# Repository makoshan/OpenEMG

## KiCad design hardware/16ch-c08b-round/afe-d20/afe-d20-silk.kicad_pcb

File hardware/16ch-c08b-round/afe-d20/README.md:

# C08B 16 通道双面采集板 `D20`（圆孔版，配螺丝壳 `R12`）

- **板框与工艺**：`43.10 × 36.50 mm`（四角 `R4.6 mm` 圆角 + 4 个 `Ø1.7 mm` 安装孔 `H901..H904`），4 层 `0.8 mm`（`JLC04081H-3313`），沉金，过孔盖油。
- **器件与接口**：正反双面双 `ADS1298` 同步采样（24 种物料共 127 颗贴片件，16 颗输入差分电容为 `22 pF` `C76924`），东南角 20P `0.5 mm` `J_AFE` 与主控板 `R4U6` 正对互联，双 34P 软板座连接 [`../strap-fpc-d2/`](../strap-fpc-d2/) 或 [`../strap-fpc-r15/`](../strap-fpc-r15/)。
- **打样与贴片投产三件套**：
  1. 工艺边拼板 Gerber：`panel/c08b-afe-d20-panel-gerber.zip`（`70.2 × 70.2 mm` 一拼一邮票孔工艺边，只传此拼板包，不传单板 `gerber/` 目录）
  2. 物料清单：`jlc_smt_bom.csv`
  3. 贴片坐标：`jlc_smt_cpl.csv`（采用单板原点，与拼板 Gerber 同坐标系；SMT 预览请核对 `V4_U2`、`V4_FPC3` 及 36 颗 ESD 极性方向）
- **三维模型与自检**：
  - 满载整板 STEP：`c08b-afe-d20-3d.step`（连接器模型随附于 `assembly/models/FPC2-fh34.step`）
  - 源板 `afe-d20-silk.kicad_pcb`（SHA-256 `31323826…`）：KiCad 10 DRC 0 违规 / 0 未连，`route_lint.py` 硬项全 0，`panel/check_panel.py` 通过。

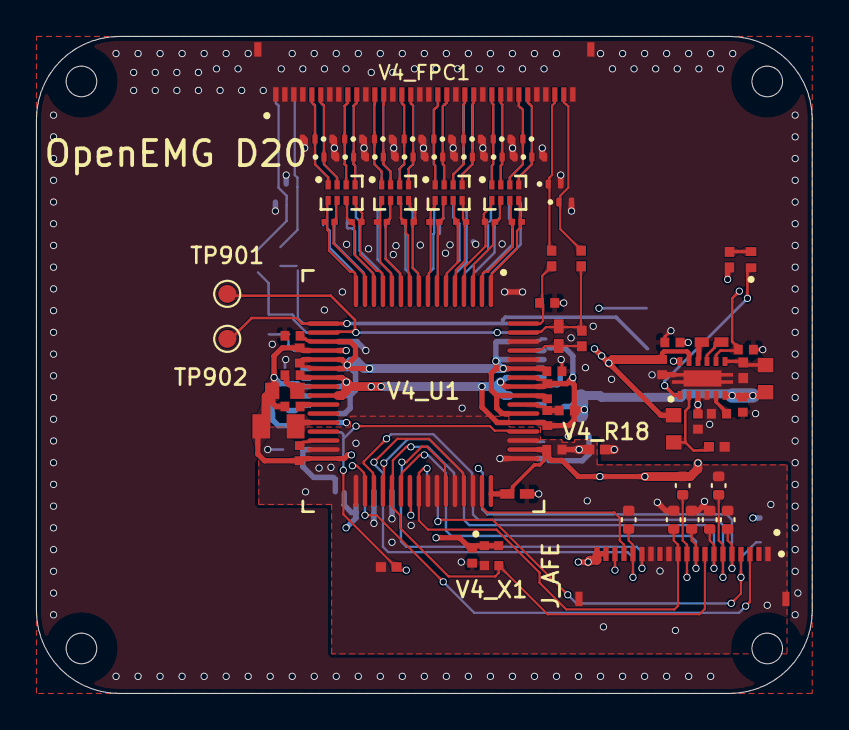
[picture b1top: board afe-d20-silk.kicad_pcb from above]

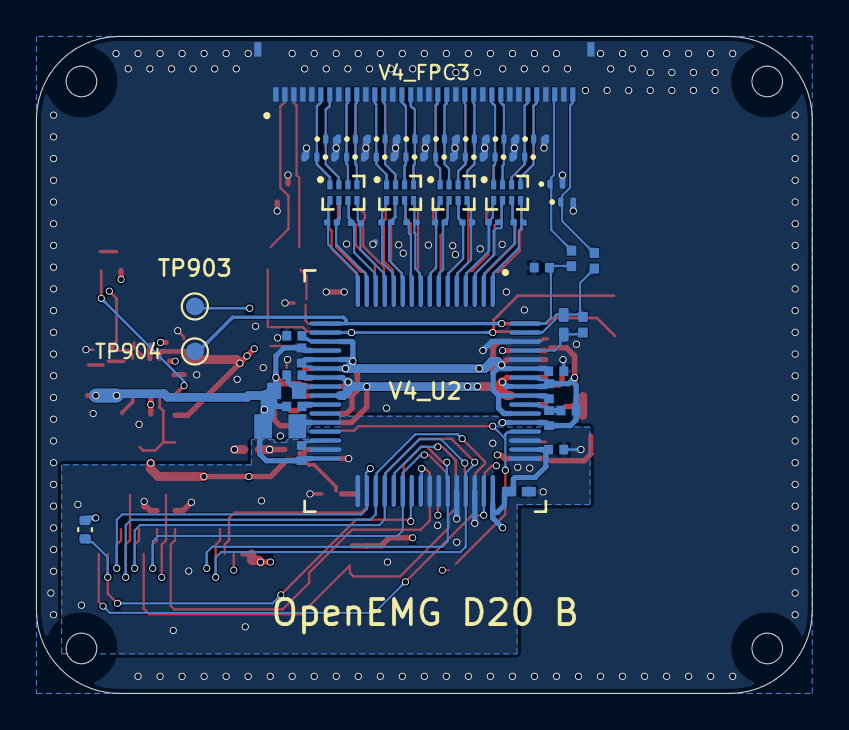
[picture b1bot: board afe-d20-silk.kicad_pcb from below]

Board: 4 copper layers, 43.1 x 36.5 mm, 135 parts (53 on the bottom side), 111 nets.

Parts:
C901: 10uF; C901
C902: 4.7uF; C902
D901: XL-1005UGC; D901
D910: ESD401DPYR; D910
D911: ESD401DPYR; D911
D912: ESD401DPYR; D912
D913: ESD401DPYR; D913
D914: ESD401DPYR; D914
D915: ESD401DPYR; D915
D916: ESD401DPYR; D916
D917: ESD401DPYR; D917
D918: ESD401DPYR; D918
D919: ESD401DPYR; D919
D920: ESD401DPYR; D920
D921: ESD401DPYR; D921
D922: ESD401DPYR; D922
D923: ESD401DPYR; D923
D924: ESD401DPYR; D924
D925: ESD401DPYR; D925
D926: ESD401DPYR; D926
D927: ESD401DPYR; D927
D930: ESD401DPYR; D930
D931: ESD401DPYR; D931
D932: ESD401DPYR; D932
D933: ESD401DPYR; D933
D934: ESD401DPYR; D934
D935: ESD401DPYR; D935
D936: ESD401DPYR; D936
D937: ESD401DPYR; D937
D938: ESD401DPYR; D938
D939: ESD401DPYR; D939
D940: ESD401DPYR; D940
D941: ESD401DPYR; D941
D942: ESD401DPYR; D942
D943: ESD401DPYR; D943
D944: ESD401DPYR; D944
D945: ESD401DPYR; D945
D946: ESD401DPYR; D946
D947: ESD401DPYR; D947
H901: M1.4 NPTH 1.7; H901
H902: M1.4 NPTH 1.7; H902
H903: M1.4 NPTH 1.7; H903
H904: M1.4 NPTH 1.7; H904
J_AFE: FH34SRJ-20S-0.5SH(50) (LCSC C2802370); Hirose_FH34SRJ-20S-0.5SH
R801: 10k; R801
R802: 10k; R802
R803: 10k; R803
R804: 10k; R804
R805: 10k; R805
R806: 10k; R806
R807: 10k; R807
R808: 10k; R808
R901: 10kΩ; R901
TP901: V4_REF2; TP901
TP902: V4_REF1; TP902
TP903: V4_REF2; TP903
TP904: V4_REF1; TP904
V4_C31: 1uF; V4_C31
V4_C32: 100nF; V4_C32
V4_C33: 1uF; V4_C33
V4_C34: 100nF; V4_C34
V4_C35: 1uF; V4_C35
V4_C36: 100nF; V4_C36
V4_C37: 100nF; V4_C37
V4_C43: 1uF; V4_C43
V4_C44: 1uF; V4_C44
V4_C45: 100nF; V4_C45
V4_C46: 10uF; V4_C46
V4_C47: 10nF; V4_C47
V4_C48: 100nF; V4_C48
V4_C49: 1uF; V4_C49
V4_C50: 100nF; V4_C50
V4_C54: 22uF; V4_C54
V4_C72: 22pF; V4_C72
V4_C73: 22pF; V4_C73
V4_C74: 22pF; V4_C74
V4_C75: 22pF; V4_C75
V4_C76: 22pF; V4_C76
V4_C77: 22pF; V4_C77
V4_C78: 22pF; V4_C78
V4_C79: 22pF; V4_C79
V4_C81: 100nF; V4_C81
V4_C82: 100nF; V4_C82
V4_C83: 2.2uF; V4_C83
V4_C84: 2.2uF; V4_C84
V4_C85: 1uF; V4_C85
V4_C86: 1uF; V4_C86
V4_C87: 100nF; V4_C87
V4_C88: 10uF; V4_C88
V4_C89: 10nF; V4_C89
V4_C90: 100nF; V4_C90
V4_C91: 1uF; V4_C91
V4_C92: 22uF; V4_C92
V4_C109: 22pF; V4_C109
V4_C110: 22pF; V4_C110
V4_C111: 22pF; V4_C111
V4_C112: 22pF; V4_C112
V4_C113: 22pF; V4_C113
V4_C114: 22pF; V4_C114
V4_C115: 22pF; V4_C115
V4_C116: 22pF; V4_C116
V4_C117: 1uF; V4_C117
V4_C118: 100nF; V4_C118
V4_C119: 1uF; V4_C119
V4_C120: 100nF; V4_C120
V4_C121: 1uF; V4_C121
V4_C122: 100nF; V4_C122
V4_C123: 100pF; V4_C123
V4_C124: 100pF; V4_C124
V4_FPC1, V4_FPC3: FH34SRJ-34S-0.5SH(50) (LCSC C424660); Hirose_FH34SRJ-34S-0.5SH
V4_LM27762: LM27762DSSR; V4_LM27762
V4_R17: 10K; V4_R17
V4_R18: 0R; V4_R18
V4_R24: 392K; V4_R24
V4_R26: 107k; V4_R26
V4_R27: 100kΩ; V4_R27
V4_R28: 100kΩ; V4_R28
V4_R29: 104k; V4_R29
V4_R32: 392K; V4_R32
V4_R34: 392K; V4_R34
V4_R35: 10K; V4_R35
V4_R36: 392K; V4_R36
V4_R37: 10K; V4_R37
V4_U1: ADS1298IPAGR; V4_U1
V4_U2: ADS1298IPAGR; V4_U2
V4_U3: 15kΩ; V4_U3
V4_U4: 15kΩ; V4_U4
V4_U5: 15kΩ; V4_U5
V4_U6: 15kΩ; V4_U6
V4_U7: 15kΩ; V4_U7
V4_U8: 15kΩ; V4_U8
V4_U9: 15kΩ; V4_U9
V4_U10: 15kΩ; V4_U10
V4_X1: 2.048MHz; V4_X1

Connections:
3V3: C901.2, J_AFE.19, J_AFE.20, R801.2, R802.2, R901.1, V4_C31.2, V4_C32.2, V4_C37.2, V4_C81.2, V4_C82.2, V4_C117.2, V4_C118.2, V4_LM27762.3, V4_LM27762.8, V4_LM27762.12, V4_U1.48, V4_U1.50, V4_U2.48, V4_U2.50, V4_X1.1, V4_X1.4
ADS_CLKSEL: J_AFE.18, V4_R17.2, V4_U1.52, V4_U2.52
ADS_CS_A: J_AFE.10, R801.1, V4_U1.39
ADS_CS_B: J_AFE.4, R802.1, V4_U2.39
ADS_DRDY_A: J_AFE.17, V4_U1.47
ADS_DRDY_B: J_AFE.3, V4_U2.47
ADS_PWDN: J_AFE.6, R804.1, V4_U1.35, V4_U2.35
ADS_RESET: J_AFE.7, R803.1, V4_U1.36, V4_U2.36
ADS_START: J_AFE.9, R805.1, V4_U1.38, V4_U2.38
AFE_CLK_IN: J_AFE.8, V4_U1.37, V4_U2.37, V4_X1.3
AFE_GPIO3: J_AFE.16, R808.1, V4_U1.45, V4_U2.45
AGND: C901.1, C902.1, D910.2, D911.2, D912.2, D913.2, D914.2, D915.2, D916.2, D917.2, D918.2, D919.2, D920.2, D921.2, D922.2, D923.2, D924.2, D925.2, D926.2, D927.2, D930.2, D931.2, D932.2, D933.2, D934.2, D935.2, D936.2, D937.2, D938.2, D939.2, D940.2, D941.2, D942.2, D943.2, D944.2, D945.2, D946.2, D947.2, V4_C33.1, V4_C34.1, V4_C81.1, V4_C82.1, V4_C83.1, V4_C84.1, V4_C119.1, V4_C120.1, V4_C123.2, V4_C124.2, V4_FPC1.1, V4_FPC1.2, V4_FPC1.3, V4_FPC1.4, V4_FPC1.7, V4_FPC1.8, V4_FPC1.11, V4_FPC1.14, V4_FPC1.17, V4_FPC1.18, V4_FPC1.21, V4_FPC1.24, V4_FPC1.27, V4_FPC1.30, V4_FPC1.31, V4_FPC1.34, V4_FPC1.MP, V4_FPC3.1, V4_FPC3.2, V4_FPC3.3, V4_FPC3.4, V4_FPC3.5, V4_FPC3.8, V4_FPC3.11, V4_FPC3.14, V4_FPC3.17, V4_FPC3.18, V4_FPC3.21, V4_FPC3.24, V4_FPC3.27, V4_FPC3.28, V4_FPC3.31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
DIN_B: J_AFE.5, R807.1, V4_U1.34, V4_U2.34
DOUT_B: J_AFE.15, V4_U1.43, V4_U2.43
GND: J_AFE.1, J_AFE.12, J_AFE.14, J_AFE.21, J_AFE.22, R803.2, R804.2, R805.2, R806.2, R807.2, R808.2, V4_C31.1, V4_C32.1, V4_C37.1, V4_C117.1, V4_C118.1, V4_R17.1, V4_R18.1, V4_U1.31, V4_U1.33, V4_U1.41, V4_U1.42, V4_U1.44, V4_U1.46, V4_U1.49, V4_U1.51, V4_U2.31, V4_U2.33, V4_U2.41, V4_U2.42, V4_U2.44, V4_U2.46, V4_U2.49, V4_U2.51, V4_X1.2
SCLK_B: J_AFE.11, R806.1, V4_U1.40, V4_U2.40
V4_$1N19: V4_C45.2, V4_C46.1, V4_U1.24
V4_$1N24: V4_C44.2, V4_U1.26
V4_$1N25: V4_C54.2, V4_U1.28
V4_$1N26: V4_C43.2, V4_U1.30
V4_$1N44: V4_C48.2, V4_C49.1, V4_U1.55
V4_$1N307: V4_C85.2, V4_U2.30
V4_$1N308: V4_C92.2, V4_U2.28
V4_$1N309: V4_C86.2, V4_U2.26
V4_$1N319: V4_C87.2, V4_C88.1, V4_U2.24
V4_$1N323: V4_C90.2, V4_C91.1, V4_U2.55
V4_$1N350: V4_C123.1, V4_R35.1, V4_U1.64
V4_$1N353: V4_C124.1, V4_R37.1, V4_U2.64
V4_$2N83: D927.1, V4_FPC1.5, V4_U6.1
V4_$2N85: D926.1, V4_FPC1.6, V4_U6.2
V4_$2N86: D925.1, V4_FPC1.9, V4_U6.3
V4_$2N87: D924.1, V4_FPC1.10, V4_U6.4
V4_$2N90: D921.1, V4_FPC1.15, V4_U5.3
V4_$2N93: D918.1, V4_FPC1.20, V4_U4.2
V4_$2N94: D917.1, V4_FPC1.22, V4_U4.3
V4_$2N95: D916.1, V4_FPC1.23, V4_U4.4
V4_$2N96: D915.1, V4_FPC1.25, V4_U3.1
V4_$2N97: D914.1, V4_FPC1.26, V4_U3.2
V4_$2N98: D913.1, V4_FPC1.28, V4_U3.3
V4_$2N111: D919.1, V4_FPC1.19, V4_U4.1
V4_$2N118: D923.1, V4_FPC1.12, V4_U5.1
V4_$2N119: D922.1, V4_FPC1.13, V4_U5.2
V4_$2N120: D920.1, V4_FPC1.16, V4_U5.4
V4_$2N121: D912.1, V4_FPC1.29, V4_U3.4
V4_$2N324: D932.1, V4_FPC3.30, V4_U7.4
V4_$2N325: D940.1, V4_FPC3.16, V4_U9.4
V4_$2N326: D942.1, V4_FPC3.13, V4_U9.2
V4_$2N327: D943.1, V4_FPC3.12, V4_U9.1
V4_$2N330: D939.1, V4_FPC3.19, V4_U8.1
V4_$2N331: D933.1, V4_FPC3.29, V4_U7.3
V4_$2N332: D934.1, V4_FPC3.26, V4_U7.2
V4_$2N333: D935.1, V4_FPC3.25, V4_U7.1
V4_$2N334: D936.1, V4_FPC3.23, V4_U8.4
V4_$2N335: D937.1, V4_FPC3.22, V4_U8.3
V4_$2N336: D938.1, V4_FPC3.20, V4_U8.2
V4_$2N337: D941.1, V4_FPC3.15, V4_U9.3
V4_$2N338: D944.1, V4_FPC3.10, V4_U10.4
V4_$2N339: D945.1, V4_FPC3.9, V4_U10.3
V4_$2N340: D946.1, V4_FPC3.7, V4_U10.2
V4_$2N341: D947.1, V4_FPC3.6, V4_U10.1
V4_$3N49: D901.2, R901.2
V4_$3N56: V4_LM27762.2, V4_R26.1, V4_R27.2
V4_$3N57: V4_C50.1, V4_LM27762.9
V4_$3N58: V4_C50.2, V4_LM27762.10
V4_$3N60: V4_LM27762.7, V4_R28.1, V4_R29.2
V4_$3N62: C902.2, V4_LM27762.5
V4_+2.5V: V4_C33.2, V4_C34.2, V4_C35.2, V4_C36.2, V4_C83.2, V4_C119.2, V4_C120.2, V4_C121.2, V4_C122.2, V4_LM27762.11, V4_R26.2, V4_U1.19, V4_U1.21, V4_U1.22, V4_U1.54, V4_U1.56, V4_U1.59, V4_U2.19, V4_U2.21, V4_U2.22, V4_U2.54, V4_U2.56, V4_U2.59
V4_-2.5V: V4_C35.1, V4_C36.1, V4_C43.1, V4_C44.1, V4_C45.1, V4_C46.2, V4_C48.1, V4_C49.2, V4_C54.1, V4_C84.2, V4_C85.1, V4_C86.1, V4_C87.1, V4_C88.2, V4_C90.1, V4_C91.2, V4_C92.1, V4_C121.1, V4_C122.1, V4_LM27762.6, V4_R29.1, V4_U1.20, V4_U1.23, V4_U1.25, V4_U1.32, V4_U1.53, V4_U1.57, V4_U1.58, V4_U2.20, V4_U2.23, V4_U2.25, V4_U2.32, V4_U2.53, V4_U2.57, V4_U2.58
V4_BIASINV1: V4_C47.1, V4_R24.1, V4_U1.61
V4_BIASINV12: V4_C89.1, V4_R32.1, V4_U2.61
V4_BIASOUT1: V4_C47.2, V4_R24.2, V4_R34.1, V4_U1.63
V4_BIASOUT12: V4_C89.2, V4_R32.2, V4_R36.1, V4_U2.63
V4_BIAS_DRV1: D910.1, V4_FPC1.33, V4_R34.2
V4_IN1N: V4_C72.1, V4_U1.15, V4_U6.7
V4_IN1N2: V4_C109.1, V4_U2.15, V4_U10.7
V4_IN1P: V4_C72.2, V4_U1.16, V4_U6.8
V4_IN1P2: V4_C109.2, V4_U2.16, V4_U10.8
V4_IN2N: V4_C73.1, V4_U1.13, V4_U6.5
V4_IN2N2: V4_C110.1, V4_U2.13, V4_U10.5
V4_IN2P: V4_C73.2, V4_U1.14, V4_U6.6
V4_IN2P2: V4_C110.2, V4_U2.14, V4_U10.6
V4_IN3N: V4_C74.1, V4_U1.11, V4_U5.7
V4_IN3N2: V4_C111.1, V4_U2.11, V4_U9.7
V4_IN3P: V4_C74.2, V4_U1.12, V4_U5.8
V4_IN3P2: V4_C111.2, V4_U2.12, V4_U9.8
V4_IN4N: V4_C75.1, V4_U1.9, V4_U5.5
V4_IN4N2: V4_C112.1, V4_U2.9, V4_U9.5
V4_IN4P: V4_C75.2, V4_U1.10, V4_U5.6
V4_IN4P2: V4_C112.2, V4_U2.10, V4_U9.6
V4_IN5N: V4_C76.1, V4_U1.7, V4_U4.7
V4_IN5N2: V4_C113.1, V4_U2.7, V4_U8.7
V4_IN5P: V4_C76.2, V4_U1.8, V4_U4.8
V4_IN5P2: V4_C113.2, V4_U2.8, V4_U8.8
V4_IN6N: V4_C77.1, V4_U1.5, V4_U4.5
V4_IN6N2: V4_C114.1, V4_U2.5, V4_U8.5
V4_IN6P: V4_C77.2, V4_U1.6, V4_U4.6
V4_IN6P2: V4_C114.2, V4_U2.6, V4_U8.6
V4_IN7N: V4_C78.1, V4_U1.3, V4_U3.7
V4_IN7N2: V4_C115.1, V4_U2.3, V4_U7.7
V4_IN7P: V4_C78.2, V4_U1.4, V4_U3.8
V4_IN7P2: V4_C115.2, V4_U2.4, V4_U7.8
V4_IN8N: V4_C79.1, V4_U1.1, V4_U3.5
V4_IN8N2: V4_C116.1, V4_U2.1, V4_U7.5
V4_IN8P: V4_C79.2, V4_U1.2, V4_U3.6
V4_IN8P2: V4_C116.2, V4_U2.2, V4_U7.6
V4_POWERGOOD: D901.1, V4_LM27762.1
V4_REF1: TP902.1, TP904.1, V4_U1.17, V4_U2.17
V4_REF2: TP901.1, TP903.1, V4_U1.18, V4_U2.18
V4_RLD_OUT2: D930.1, V4_FPC3.34, V4_R36.2
V4_WCT: D911.1, V4_FPC1.32, V4_R35.2
V4_WCT2: D931.1, V4_FPC3.32, V4_R37.2

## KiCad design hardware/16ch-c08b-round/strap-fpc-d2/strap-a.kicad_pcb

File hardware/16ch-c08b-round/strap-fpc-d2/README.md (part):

# 表带软板 D2：配合「表带电极层 D2」的四层 34P 双片（2026-11-11）

**状态：已实现未验收。** 本机 DRC 两片 0/0（含重铺）、几何、脚序、对孔、壳外方案的尾巴缝检查全过（`checks.json` 30 项门全部 `ok`，`fails: []`；11-11 晚「胶囊段移到底壳外」改版，见 §0000），满载三维模型 `strap-a-3d.step`（36 实体，含 `EB1/EB2A` 方形 `3×3×2 mm` 铜块）与 `strap-b-3d.step`（34 实体，`EB2` 层间对焊盘不挂铜块）经 `fit_3d_check.py`（`fit-3d.json`）逐实体刚体变换核验 `A+B` 叠层与 `tray_d2`、`cap_d2` 及 `A∩B` 层间布尔干涉均为 `0.0 mm³`（6 颗铜片尖端齐平 `Z = -2.256 mm` 外露 `1.20 mm`，4 组必交反例全红），`fab/` 嘉立创 FPC + SMT 制造包已出齐（`strap-a-gerber.zip` `b7aa2a09`、`strap-b-gerber.zip` `43175156`，含拆分 `0.10mm / 0.20mm` 实心 PI 补强 Gerber、IPC-D-356、全基础库 BOM/CPL，经 `gnet_fpc.py` 像素级反推 0 断 0 短 + 6 反例全红）；未打样、未焊铜片、未插采集板、未贴肤、未装底盖。基于 R15（`../strap-fpc-r15/`）生成器改写。R15、R12、采集板、TPU 层、制造包都没动。

叠层（表带 → 皮肤）：25 mm 表带 → 本软板（背胶贴表带，F 面焊盘朝皮肤）→ 0.8 TPU 开孔层（孔 Φ6.5，`tpu-layer-d2/`）→ Φ6×2.0 镀金铜片回流焊在 F 面焊盘上。

生成：KiCad 自带 python3 跑 `build.py` → `check.py`（写 `checks.json`，有失败退出码 1）→ 系统 python3 跑 `preview.py`。UUID 每次会变，以 `checks.json` 的 `board_sha256` 为准。

## 11-12 REF 挪到 A 片（Mako 定）

辅点铜片改方形 3×3×2（Φ4×2 买不到）后，B 片 EB2 焊盘比 A 片低一层，REF 只凸出 1.0、其它 1.2。REF（BIAS_DRV12）只在 B 尾 FPC3 34 脚有，A 尾 FPC1 没这个脚，不改 D17 就不能在 A 片单走。做法：A 片 EB2 位置原 Φ4.9 让位孔换成 **EB2A**——Φ4.5 焊盘、Φ0.8 金属化孔、两面开窗；B 片 EB2 焊盘贴在它背面同心，装配时 A/B 叠好对正、从 A 片 F 面往孔里灌锡把两片焊通，再焊铜片。6 个贴肤焊盘都在 A 片 F 面，同高。

- 新门 `eb2_joint`：读两块板实物，EB2A 与 B 片 EB2 同心 ≤ 0.01、同 Φ4.5、同网 BIAS_DRV12_E、金属化孔 0.6–1.0、两面开窗、A 片附近无板边孔；反例「右移 0.05」「网改 AGND」全红。
- `stack_clearance` 撤掉「A 让位孔 vs B 的 EB2」一项（现在是有意对焊）。
- 全部门绿，DRC A/B 0/0。
- 未验：灌锡对焊没试；焊点厚度没算进叠层；锡要灌到和焊盘持平，鼓包会把方块铜片垫斜，焊完先量高再焊铜片。EB2A 故意不开 F 面钢网（锡膏不进孔）；内层 AGND 到焊盘 0.151（规则 0.15）。

## 0000. 胶囊段移到底壳外（11-11 晚 Mako 定）

上一轮复核：胶囊段在 R13 底壳里（Z 1.00 起）会顶到 D17 底面件（U2 底 Z 1.24，叠放顶 1.406，−0.166；V4_FPC3 −0.086；单片在 U2 下也只有 0.037）。Mako 定：胶囊段整段放到底壳外，贴外底（Z 0.15），外面再扣一块 0.8 平底盖，铜片从盖孔穿出。叠层（R13 盒坐标，Z 朝表带）：底壳外底 0.15 → B 片 → A 片 → 底盖（顶面 −0.256）。触点位置、焊盘直径、表带 28 路、对孔、`f_res_pockets` 都没变。

| 项 | 做法 / 数 |
|---|---|
| 尾巴加长 | **1.30 mm**（两片同）。原回折路径不变，只是「离开底面往上拐」那一弯下移 ΔZ = 1.1015 − (−0.1545) = 1.256（A；B 同），竖直段多 1.256，取 1.30。金手指整排、尾补强随尖端沿 −x 平移：A 尖 30.16 → 28.86，B 32.39 → 31.09；尾折弯动态区延到弯折线 39.96 |
| 弯折线 | 板 x 39.96 = 盒 Y 18.04（V4_FPC1/FPC3 北沿）：尾从这里离开壳外平面，B 在内、A 在外同心上拐（内侧 R0.5），竖直中线 B 18.64、A 18.84，再按原回折进座子 |
| `tray_tail_slot` | 盒 x −8.95…8.95、y 17.99…19.00，穿底板 Z 0.15…1.00。A 尾外表面到 Y 18.945，**超过原北回折槽北壁 18.80，槽要退到 ≥ 19.00（Z 1.00–4.10）** |
| 为让尾在 39.96 处只剩尾宽 | A 头部下角斜边起点 39.5 → 40.0；A、B 尾部地过孔从 39.77 / 39.24 挪到 40.3（弯折区不放孔）；A 北支换层孔 x 40.6/41.8 → 41.2/42.4；B 片 BIAS_DRV12 换层孔 40.2 → 41.0；A 34 脚地孔 (40.2, 58.25) → (40.6, 58.25)；B 头部换道起点 39.4 → 40.06 |
| A 北支 | 与尾之间原有 0.4 缝（到 x 40.0），北支留在壳外平面，不进缝 |
| `capsule_stack` | 胶囊范围（板 x 39.96–76.8）A∩B 叠放区，盒坐标 1 个多边形，379.17 mm²；叠放处 B 在外底与 A 之间 |
| `capsule_res_pockets`（新） | 胶囊串阻在 FPC 背面朝底壳，底壳外底要挖浅槽：A 片 R1–R4 槽深到 Z 0.347、R33 到 0.447；B 片 R34 到 0.65（高度为假设） |

门：
- `box_height`（改）：① 每片外形在弯折线以北拆成连通块，带金手指的那块（尾）在弯折线处落在缝宽内（A −8.455…8.75、B −8.75…8.75），其余块（A 北支）留壳外；② 尾竖直段对 D17 底面件包围盒间隙 ≥ 0.05（最近 A 尾对 V4_FPC3 0.703；B 尾插 V4_FPC3 本身不算）；③ 胶囊范围 FPC 全在壳外（Z ≤ 0.15），原 U2/C92/V4_FPC3 叠放项消失。反例 2 个（补上北支与尾之间的缝、B 尾加宽到 y 60）都判红。
- `pins_a/b`：与 R12 金手指比几何时扣掉 1.30 平移；`tail_vs_r12` 另核实测平移量 = 1.30。

实测：DRC A/B 0/0、重铺 0/0；route_lint 硬项 0/0；等长 32 段 0 mil；对孔 0 误差；板 SHA256 前 12 位 A/B a0f99b2550f7 / ee886a565cdf。

假设 / 未验证：座子插口高度取包围盒中线（A 3.955、B 1.945），只用于尾竖直段对底面件的间隙；ΔZ 按标称板厚 0.203；串阻槽深按 0402 0.35、0603 0.45；A 片背面不叠 B 的地方与底壳外底之间有 0.203 空隙，底壳外底是否做台阶由底壳方定（`capsule_stack` 给了叠放区）。

## 000. 胶囊底改 SMD 焊盘 + 底片（11-11 晚，本次改版）

Mako 定：照商用肌电手环，胶囊底扣一块单独的底片，底片开 6 个孔，电极用和表带一样的镀金铜片；之后又定 EB1/EB2（BIAS/REF）用 Φ4 铜片（Φ4×1.5 + Φ4×0.8 叠焊）。

| 项 | 上一版（§00，R15 原样） | 本版 |
|---|---|---|
| 胶囊底 6 个触点 | Ø1.8 焊盘 + Ø1.0 PTH（铆钉） | **F 面圆形 SMD，无孔，开窗 = 焊盘**；CH1/CH2 四个 **Φ6.5**（焊 Φ6×2.0），EB1/EB2 **Φ4.5**（焊方形 3×3×2，11-12 改）；中心与 R15 同位（误差 0） |
| 触点 PI 补强 | 无 | 仍无：胶囊段平躺在底壳/底片上不弯，铜片靠底片孔定位；补强只会把胶囊段再垫高 0.2 |
| 让位孔 | A (50.5, 50) Ø2.2、B (65.5, 50) Ø2.2 | **都撤了**（11-12）：A 片 EB2 处原 Φ4.9 让位孔换成 EB2A 对焊焊盘；B 片 EB1 让位孔早已删掉 |
| 串阻（仍 B 面，同值同网） | R15 原位 | 挪位（下表）：原位挡住 B 片绕 EB2 的走线和 A 片穿胶囊的 B 面带 |
| A 片 CH1 | F 面绕 EB2 让位孔（11-12 起该处是 EB2A 焊盘） | F 出尾 → 过孔换 B → B 面 y 44 过 E1N 背后 → 两列之间 x 57 分叉：N 留 B 上行到 R2，P 打孔到 F 下行（跨 B 面带）→ 过孔 → B 面到 R1 |
| A 片 CH2 | F 面绕让位孔下方 | F 面 y 46 从 E1N 与 EB2（11-12 起是 EB2A 焊盘）之间穿过 → x 60.2 分叉：N 打孔到 B 上行到 R4，P 留 F 下行 → 过孔 → B 面到 R3 |
| A 片 CH5–8 | F 面 A_HEAD 道穿胶囊 | 胶囊 F 面被焊盘占满，改 **B 面** A_LOW 道（y 54.0/55.2/56.4/57.6）：C1 列左侧 x 45.5 换 B，C2 列右侧 x 69.6 换回 F（每次换层两线各多 0.65，等长不受影响） |
| A 片 BIAS_DRV1 | F 面 y 60 → (69, 60) 过孔 | F 出尾 → 过孔 (46.8, 58.6) → B 面到 R33 → 过孔 (61.6, 58.6) → F 竖直上行进 EB1 |
| B 片 8 对 | 绕 Ø1.8 EB2 | 绕 EB2 上下各 4 对（CH16–13 / CH12–9），关于 y 50 对称，x 54.6 后收拢到原并行段；B 头部外形 y 43.355–56.645 |
| B 片 BIAS_DRV12 | B 面沿头部上沿到 R34 | B 面竖直下到 y 50 → R34（EB2 左侧）→ 过孔 (47.5, 50) → F 短线进 EB2 |
| 电极侧接法 | 端子 PTH 直连 | 串阻电极侧 → B 面短线 → **焊盘圆外**过孔 → F 面短线伸进焊盘 0.3（不做盘中孔；过孔铜到焊盘铜最小 A 0.248、B 0.50（胶囊）） |

串阻挪位（板坐标，`checks.json` → `box_vs_r15.resistors`）：

| 件 | 网 | R15 | 本版 | 挪动 |
|---|---|---|---|---|
| R2 | CH1_N | (50.5, 43.6) | (50.5, 39.5) | 4.1 |
| R1 | CH1_P | (50.5, 56.2) | (50.5, 60.5) | 4.3 |
| R4 | CH2_N | (65.5, 43.6) | (65.5, 39.5) | 4.1 |
| R3 | CH2_P | (65.5, 56.2) | (65.5, 60.5) | 4.3 |
| R33 | BIAS_DRV1 200k | (69.0, 54.8) | (59.4, 58.6) | 10.32 |
| R34 | BIAS_DRV12 200k | (53.5, 50.0) | (45.5, 50.0) | 8.0 |

全部仍在 B 面（胶囊里面）、横放；A 片的都落在 B 片外形外 ≥ 0.3（`stack_clearance`）；R34 在 B 片背面。

`geometry.json` → `capsule_pads`（盒坐标按 R13 壳：盒 X = 板 y − 50、盒 Y = 58 − 板 x）：

| 件 | 片 | 网 | 焊盘 | 板坐标 | 盒坐标 (X, Y) |
|---|---|---|---|---|---|
| E1N | A | CH1_N_E | Φ6.5 | (50.5, 42) | (−8, 7.5) |
| E1P | A | CH1_P_E | Φ6.5 | (50.5, 58) | (8, 7.5) |
| E2N | A | CH2_N_E | Φ6.5 | (65.5, 42) | (−8, −7.5) |
| E2P | A | CH2_P_E | Φ6.5 | (65.5, 58) | (8, −7.5) |
| EB1 | A | BIAS_DRV1_E | Φ4.5 | (65.5, 50) | (0, −7.5) |
| EB2 | A（EB2A，金属化孔 Φ0.8，B 面对焊 B 片 EB2） | BIAS_DRV12_E | Φ4.5 | (50.5, 50) | (0, 7.5) |

底盖（`../../enclosure-46x40/c08b-shell-r12/capsule-cap-d2/`）已按本节 `capsule_pads` 对齐 EB1/EB2 方形孔位与圆孔位，并由 `fit_3d_check.py` 完成三维实体布尔零干涉校验。

凸出（假设标称厚度，未实测）：11-12 起 6 个贴肤焊盘都在 A 片 F 面，从 A 片 F 面算铜片尖都是 2.0（`capsule_pads.stack_note`）。

新门 / 改门：
- `box_vs_r15`（改）：6 个触点中心与 R15 同位（≤ 0.01）且是 F 面 SMD 圆、无孔、开窗 = 焊盘、直径对（CH Φ6.5 / EB Φ4.5）；R1–R4/R33/R34 同值、同网、仍在 B 面，位置只报告。反例 4 个（E1N 右移 0.05、R33 改 100k、R4 尾侧网改 CH1_N、EB1 焊盘改 Φ1.8）全红。
- `stack_clearance`：「B 外形 vs A 的 EB1 端子」删掉（EB1 不再穿 B 片）；「A 让位孔 vs B 的 EB2」11-12 撤掉（改为 `eb2_joint` 对焊门）。
- `pad_edge_and_no_via_in_pad`：触点集合由 r > 3 改为 r > 2，把 Φ4.5 的 EB 焊盘也收进来（门值没动）。

实测（`checks.json`）：DRC A/B 0 违规 0 未连，重铺后也 0/0；route_lint 硬项 0/0；等长 32 段全部 0.000 mil（CH1/CH2 电极侧几何对称、尾侧腿上凸起 0.121/0.483）；异网中心距 A 0.4994、B 0.495；走线到让位孔边 0.325 以上（11-12 前的数）；`f_res_pockets` 28 个、`capsule_pads` 6 个。板 SHA256 前 12 位：A/B 3d266349ac96 / 556502bbcb4a（含 R34 右移）。

预览：`preview-capsule-a.png`、`preview-capsule-b.png`、`preview-capsule-ab.png`（两片叠看）。

未验证：底片、铜片、焊盘均未打样；A/B 两片在 EB2 处灌锡对焊没试过（锡能不能从 Φ0.8 孔流到背面焊满、焊点会不会把两片垫高）。

## 00. CH1/CH2 回表盘底（11-11 晚，本次改版）

Mako 定：「改回原来方案，触点在表盘底部」。

| 项 | 上一版 | 本版 |
|---|---|---|
| CH1/CH2 | 北片 x 8 / x 0 两个 Φ6.5 新岛 | **回胶囊底**：E1N/E1P (50.5, 42/58)、E2N/E2P (65.5, 42/58)，Ø1.8 焊盘 + Ø1.0 孔，对内 16.0；串阻 R1–R4（B 面 0402 100k）；F 面绕 EB2 让位孔 → 过孔 → B 面腿（凸起调等长）→ 串阻 → B 面短线进端子。触点、串阻、走线、过孔全部按 R15 生成器原样搬回 |
| 北片 | 4 岛（x 24/16/8/0） | **2 岛**：CH3（x 24，表带 Y 34）、CH4（x 16，Y 42）；x 8/x 0 岛与北支延伸删除；北支宽度仍 36.9–40.85，两对等分（中心 37.89/39.86） |
| 表带 14 路 | — | 不变：F 面 Φ6.5、F 面串阻、B 面 PI Φ7.2×0.20、26.2 高岛、映射 X = 50 − 板 y、Y = 58 − 板 x |
| D17 34P 脚序 | — | 不变（CH1 仍 A 5/6 脚） |

新门 / 改门：
- `box_vs_r15`（新，替代 `box_aux_vs_r15`）：A 片 E1N/E1P/E2N/E2P/EB1/R1–R4/R33、B 片 EB2/R34 的坐标、面、值、焊盘（含孔、层）、网与 R15 逐个相同；CH1/CH2 全部 58 段走线、4 个过孔与 R15 逐段相同。反例 3 个（R2 右移 0.1、R33 改 100k、CH1_N_E 端点挪 0.05）全红。
- `contacts_d2`：表带 28 个 Φ6.5 SMD 焊盘；串阻面按路区分（CH1/CH2 B 面，其余 F 面）；两片串阻合计仍 34 颗（A 17、B 17）。
- `tpu_hole_alignment`：北排在 check 里写死期望 (34, 42)，同时报 TPU 文件里的值（当前 TPU build.py 已是 (34, 42)，一致）；28 焊盘对 28 孔，最大误差 0.00000。
- `strapside_flat` 只算表带 14 岛（胶囊底 R1–R4/R33/R34 只报告）；`skinside_res_envelope` 只收表带 28 颗 F 面串阻（`f_res_pockets` 28 个，2.16×1.24，离焊盘最小 0.8516）；`stiffener_inside_island` 由「≥17」改为精确等于「表带触点数 + 1」（A 13、B 17），没放宽。

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
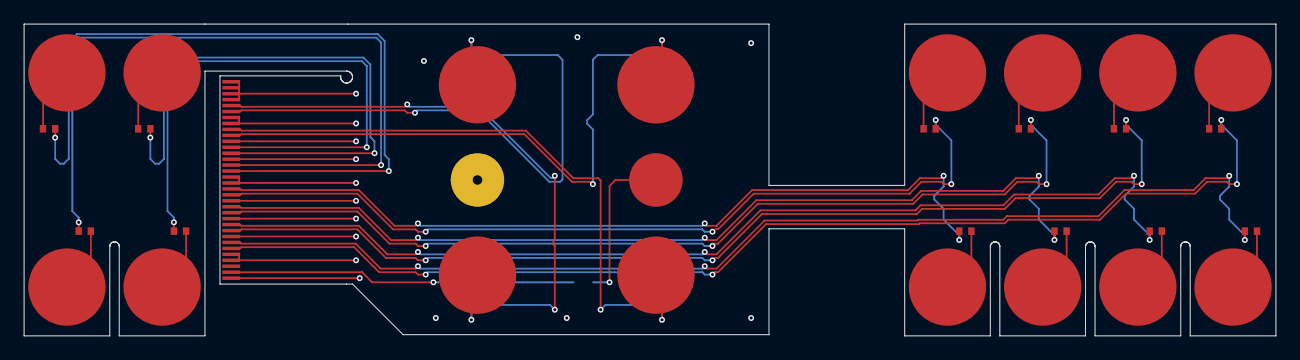
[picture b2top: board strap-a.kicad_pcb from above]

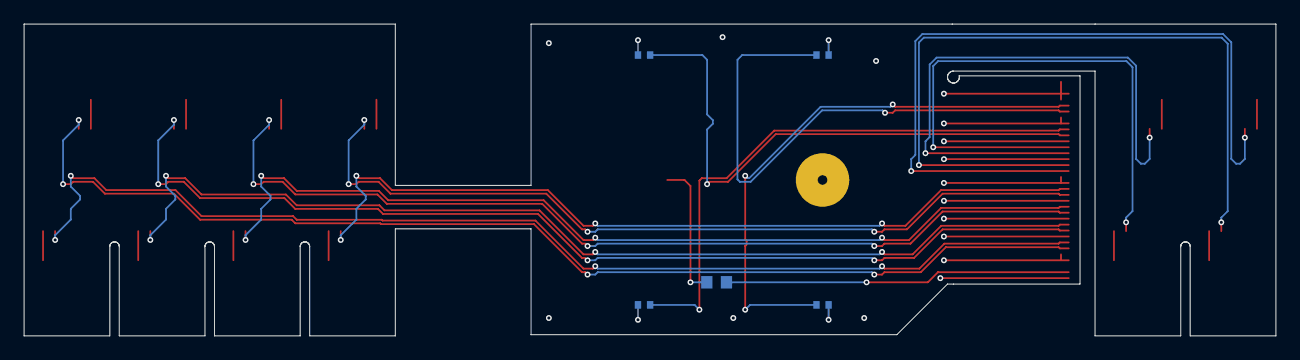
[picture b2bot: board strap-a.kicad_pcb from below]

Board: 4 copper layers, 105.2 x 26.2 mm, 36 parts (5 on the bottom side), 35 nets.

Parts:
E1N, E1P, E2N, E2P, E3N, E3P, E4N, E4P, E5N, E5P, E6N, E6P, E7N, E7P, E8N, E8P: 贴肤焊盘（焊 Φ6×2.0 镀金铜片）; CONTACT_SMD_D6.5
EB1: 贴肤焊盘（焊方形 3×3×2 镀金铜片）; CONTACT_SMD_D6.5
EB2A: REF 贴肤焊盘（焊方形 3×3×2，孔内灌锡对焊 B 片 EB2）; CONTACT_D1.8
R1, R2, R3, R4, R5, R6, R7, R8, R9, R10, R11, R12, R13, R14, R15, R16: 100k; R0402
R33: 200k; R0603
TAIL_A: D17 V4_FPC1; FPC34_P0.5_TAIL

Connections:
AGND: TAIL_A.1, TAIL_A.2, TAIL_A.3, TAIL_A.4, TAIL_A.7, TAIL_A.8, TAIL_A.11, TAIL_A.14, TAIL_A.17, TAIL_A.18, TAIL_A.21, TAIL_A.24, TAIL_A.27, TAIL_A.30, TAIL_A.31, TAIL_A.34
BIAS_DRV1: R33.1, TAIL_A.33
BIAS_DRV1_E: EB1.1, R33.2
CH1_N: R2.1, TAIL_A.6
CH1_N_E: E1N.1, R2.2
CH1_P: R1.1, TAIL_A.5
CH1_P_E: E1P.1, R1.2
CH2_N: R4.1, TAIL_A.10
CH2_N_E: E2N.1, R4.2
CH2_P: R3.1, TAIL_A.9
CH2_P_E: E2P.1, R3.2
CH3_N: R6.1, TAIL_A.13
CH3_N_E: E3N.1, R6.2
CH3_P: R5.1, TAIL_A.12
CH3_P_E: E3P.1, R5.2
CH4_N: R8.1, TAIL_A.16
CH4_N_E: E4N.1, R8.2
CH4_P: R7.1, TAIL_A.15
CH4_P_E: E4P.1, R7.2
CH5_N: R10.1, TAIL_A.20
CH5_N_E: E5N.1, R10.2
CH5_P: R9.1, TAIL_A.19
CH5_P_E: E5P.1, R9.2
CH6_N: R12.1, TAIL_A.23
CH6_N_E: E6N.1, R12.2
CH6_P: R11.1, TAIL_A.22
CH6_P_E: E6P.1, R11.2
CH7_N: R14.1, TAIL_A.26
CH7_N_E: E7N.1, R14.2
CH7_P: R13.1, TAIL_A.25
CH7_P_E: E7P.1, R13.2
CH8_N: R16.1, TAIL_A.29
CH8_N_E: E8N.1, R16.2
CH8_P: R15.1, TAIL_A.28
CH8_P_E: E8P.1, R15.2

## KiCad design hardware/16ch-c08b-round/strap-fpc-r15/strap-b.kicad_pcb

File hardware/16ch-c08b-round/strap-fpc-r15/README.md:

# R15 表带软板：D17 采集板 34P、四层、盒外 14 岛对内 18.0 mm（Meta 专利参考，2026-11-08）

**状态：已实现未验收（未打样、未插实物）。** 基于前序 R14 迭代，将**盒外 14 个电极岛（北 2 岛 CH3–CH4 + 南 12 岛 CH5–CH16）**的对内（同路 P/N，沿前臂肌纤维纵向）中心距从 `16.0 mm`（`y = 42.0 / 58.0 mm`）外扩至 **`18.0 mm`（`y = 41.0 / 59.0 mm`）**，同时将盒外岛外形高收窄至 **`21.2 mm`（`y = 39.4–60.6 mm`，补强高 `20.8 mm`）**，完美适配卡尺实测的 **`22.04 mm` 表带**（两侧各留 `0.42 mm` 余量，同时也兼容 `25 mm` 表带）；保持**盒底 2 对（CH1/CH2，`16.0 mm`）+ 2 辅助（EB1/EB2）及串阻原位不动**（100% 兼容透明光固化外壳 `../../enclosure-46x40/c08b-shell-r12/` 与 `c08b-shell-r13-notch/` 的 `22.30 mm` C 形生耳槽），并保持**腕周节距 `8.0 mm`**（16 路跨度 `166.8 mm`，适配 `≥ 162 mm` 腕围）。

生成：KiCad 自带 python3 跑 `build.py`（两块板 + 填好的 GND 平面 + pro/dru + `d17-interface.csv`、`geometry.json`、`match.json`）→ `check.py`（全部检查，写 `checks.json`，有失败退出码 1）→ 系统 python3 跑 `preview.py`（PNG）。每次重跑 UUID 会变，以 `checks.json` 里的 `board_sha256` 为准。

## 1. 与 Meta sEMG-RD 专利/论文及 R14 间距对照

| 维度 | Meta sEMG-RD（Nature 2025 / US20230397856A1） | R14（`c08b-d17-fpc34-4l-r14`） | R15（本目录 `meta18`） | R15 机械与电生理收益 |
|---|---|---|---|---|
| **对内中心距（同路 P–N，沿肌纤维纵向）** | **20.0 mm** | 16.0 mm（`y=42/58`） | **盒外 14 岛 18.0 mm（`y=41/59`）**<br>盒底 2 对 16.0 mm（`y=42/58`） | 盒外 14 岛达 Meta 中心距的 **90%**，差分体积导体对深层指伸/指屈肌动作电位的拾取幅度约增 **+10%–12%**（理论估算，未实测） |
| **同路两触点内侧边到边净距** | `20.0 − 6.5 =` **13.5 mm** | `16.0 − 4.0 = 12.0 mm` | 表带 14 岛 `18.0 − 1.5 =` **16.5 mm**（`Φ1.5×Φ0.8×2.0 mm` 黄铜铆钉触点，杆 `Φ0.80 mm` 穿 `Ø1.00 mm` PTH 孔先焊后装）<br>盒底 2 对 `16.0 − 4.0 = 12.0 mm`（`Ø4.0` 大触点） | 表带同对触点内侧边到边净距达 **16.5 mm > Meta 13.5 mm**，出汗贴肤时同对电极间表面汗液短路阻抗更高 |
| **盒外电极岛补强宽 / 岛外形高** | 刚性壳体约 25 mm | 补强 `19.6 mm`（`40.2–59.8`）<br>PCB `20.0 mm`（`40.0–60.0`） | **补强 `20.8 mm`（`39.6–60.4`）**<br>**PCB `21.2 mm`（`39.4–60.6`）** | 装入实测 **22.04 mm 表带**两侧各留 **0.42 mm** 余量（装 25 mm 弹力带两侧各留 1.9 mm） |
| **腕周相邻通道节距（沿腕围横向）** | S 码 **10.6 mm** / M 11.9 / L 13.3 | **8.0 mm** | **8.0 mm** | 16 路端到端跨度 **166.8 mm**（对标 Meta S 码 169.6 mm），适配 **≥ 162 mm** 腕围，北岛 `CH4` 与南末岛 `CH16` 绕腕不撞车 |
| **正背面走线经过串阻焊盘** | — | A 17 处（含南岛 `R9/R11`）、B 20 处（`R18–R28`） | **盒外 14 岛 0 处**（B 全片 **0 处**；A 仅盒底 `R1/R3/R33` 13 处） | 外扩 1.0 mm 配合 `A_ISL_MAX=55.8` 与 `B_BR=(43.32, 49.5)`，盒外全部 28 颗 0402 串阻正背面走线叠焊盘彻底归零 |

## 2. 规则与实测（`checks.json` 全部 23 项 `ok: true`，`fails: []`）

| 要求 | R15 做法 | 本机实测（`checks.json`） |
|---|---|---|
| 脚序对上 D17 V4_FPC1 / V4_FPC3 | `build.py` 和 `check.py` 各自直接读 D17 源板，采样网沿 15k 阵列（V4_U3–U10）追到 ADS1298 的 `V4_INx[PN](2)`，换成 CHn_P/N | 两片各 34 脚，与 D17 逐脚 **0 差**；与 R12 的信号脚、金手指坐标/尺寸也 0 差 |
| 四层：顶 / GND / GND / 底 | F.Cu 信号、In1.Cu AGND、In2.Cu AGND、B.Cu 信号；AGND 金手指在折弯区后打孔进两层平面 | 两层平面各 1 块连通铜，孤铜 0 |
| 加宽、组间拉开 | 每段带都比 R12 宽；带内各对等分（见 §4） | 逐段 ≥ R12；同一 TPU 槽 A+B 合计 14.12（R12 11.17） |
| 线宽 0.15 | 全板一种线宽 | 0.15 |
| 对内中心距 0.30 | 对内净距 0.15 | 最小 0.300 |
| 不同对两线中心距 ≥ 0.47（> 18 mil） | DRC 规则「不同网走线（同一差分对除外）净距 ≥ 0.32」= 中心距 0.47；AGND/BIAS 线也算 | 读文件量：A 0.500、B 0.4825（B 盒内头部，静态区） |
| 最外侧铜到板边 ≥ 0.305 | DRC `edge_clearance 0.305`；排道时按 0.315 留 | 走线铜到外形 A 0.315、B 0.312；到让位孔边 A 0.375、B 0.325 |
| 触点与串阻：盒底同 R12、盒外 18 mm | 盒底 6 触点 + 6 串阻原位不动；盒外 14 岛（28 触点 + 28 串阻）向南北各外扩 1.0 mm | 盒底 12 器件与 R12 **0 差**；盒外 56 器件外扩 ±1.0 mm 后与 R12 归一化 **0 差** |
| 尾尖、尾宽、金手指、补强同 R7/R12 | 尾宽 17.5、金手指 0.3×1.5 节距 0.5 离尖端 0.2、F 面；补强 2.5 在 B 面（金手指背面）；A 尖端 x 30.16、B 32.39 | 尾宽 17.5 = R12；补强长 2.5；金手指与 R12 逐脚相同 |
| 0/45/90° | 换道一律 45° 斜线，拐角 135° | route_lint 怪角度 0、尖角 0 |
| P/N 分段等长 ≤ 10 mil | 南岛、盒底：B 面腿上 45° 凸起；北岛：分叉线整体下移解析求等（CH3 +0.4435、CH4 +0.3192 mm，不加凸起） | 32 段里 30 段差 0.000；A CH1、CH2 电极侧 7.874 mil（见 §5） |

## 3. 插接尾与脚序

| 脚 | A → V4_FPC1 | B → V4_FPC3 |
|---|---|---|
| CH 对 (P/N) | 5/6 CH1、9/10 CH2、12/13 CH3、15/16 CH4、19/20 CH5、22/23 CH6、25/26 CH7、28/29 CH8 | 6/7 CH9、9/10 CH10、12/13 CH11、15/16 CH12、19/20 CH13、22/23 CH14、25/26 CH15、29/30 CH16 |
| 辅助 | 33 BIAS_DRV1 → 200k → EB1 | 34 V4_RLD_OUT2（BIAS_DRV12）→ 200k → EB2 |
| 空（只留金手指） | 32 V4_WCT | 32 V4_WCT2 |
| AGND（打孔进 In1/In2） | 其余 16 脚 | 其余 16 脚 |
| 1 脚位置 | 小 y（41.75） | 大 y（58.25） |

全表 `pin-map.json`、`d17-interface.csv`（含阵列脚、ADC 脚）。金手指面、1 脚方向同 R7/R12/R14（两片都在 F 面）。

## 4. 带宽：R12 vs R15 逐段（同一 x 截面，读两块板文件量；`widths.csv`）

| 段（x） | R12 y 范围 | R12 宽 | R15 y 范围 | R15 宽 | 增 | R12 对中心距 / 最近异网线中心距 | R15 对中心距 / 最近异网线中心距 | R15 外侧铜到边 上/下 |
|---|---|---|---|---|---|---|---|---|
| 插接尾（35.0 / 36.5，8 对） | 41.25–58.75 | 17.5 | 41.25–58.75 | 17.5 | 0 | 1.5–2.0 / 1.16–1.18 | 1.5–2.0 / 0.50（AGND 线） | 1.425 / 0.425 |
| A 北支（33） | 39.25–40.85 | 1.60 | 38.95–40.85 | 1.90 | +0.30 | 0.68 / 0.34 | 0.82 / 0.52 | 0.315 / 0.315 |
| A 北颈（20） | 44.88–50.725 | 5.845 | 同 | 5.845 | 0 | 1 对 | 1 对 | 4.895 / 0.50 |
| A 出盒带（80） | 50.725–56.05 | 5.325 | 53.30–59.00 | 5.70 | +0.375 | 0.64 / 0.32 | 1.425 / 1.125 | 0.487 / 0.487 |
| A 桥1（94） | 同上 | 5.325 | 同上 | 5.70 | +0.375 | 0.64–2.12 / 0.32 | 1.90 / 1.60 | 0.725 / 0.725 |
| A 桥2（102） | 同上 | 5.325 | 同上 | 5.70 | +0.375 | 2.76 / 2.10 | 2.85 / 2.55 | 1.20 / 1.20 |
| A 桥3（110） | 同上 | 5.325 | 同上 | 5.70 | +0.375 | 1 对 | 1 对（贴上侧） | 0.315 / 4.935 |
| B 盒内头部（60） | 44.8–52.6 | 7.80 | 44.68–53.79 | 9.11 | +1.31 | 0.64–3.1 / 0.32 | 0.782–3.3 / 0.4825 | 0.315 / 0.315 |
| B 与 A 并行（80、94、102、110、118） | 44.88–50.225 | 5.345 | 44.88–52.80 | 7.92 | +2.575 | 0.64 / 0.32 | 0.977 / 0.677 | 0.315 / 0.315 |
| B 桥1（126，7 对） | 44.88–50.225 | 5.345 | 43.32–49.50 | 6.18 | +0.835 | 0.64 / 0.32 | 0.850 / 0.550 | 0.315 / 0.315 |
| B 桥2（134，6 对） | 同上 | 5.345 | 同上 | 6.18 | +0.835 | 0.64 / 0.32 | 1.020 / 0.720 | 0.315 / 0.315 |
| B 桥3（142，5 对） | 同上 | 5.345 | 同上 | 6.18 | +0.835 | 0.64 / 0.32 | 1.236 / 0.936 | 0.393 / 0.393 |
| B 桥4（150，4 对） | 同上 | 5.345 | 同上 | 6.18 | +0.835 | 0.64–0.775 / 0.32 | 1.545 / 1.245 | 0.547 / 0.548 |
| B 桥5（158，3 对） | 同上 | 5.345 | 同上 | 6.18 | +0.835 | 0.64–1.21 / 0.32 | 2.060 / 1.760 | 0.805 / 0.805 |
| B 桥6（166，2 对） | 同上 | 5.345 | 同上 | 6.18 | +0.835 | 1.85 / 1.19 | 3.090 / 2.790 | 1.320 / 1.320 |
| B 桥7（174，1 对） | 同上 | 5.345 | 同上 | 6.18 | +0.835 | 1 对 | 1 对（居中） | 2.865 / 2.865 |
| **同一 TPU 槽 A+B（80/94/102/110）** | 44.88–56.05 | **11.17** | 44.88–59.00 | **14.12** | **+2.95** | A 5.325 + B 5.345 + 缝 0.5 | A 5.70 + B 7.92 + 缝 0.5 | |

## 5. 分段等长（KiCad 读回走线长度，`lengths.csv`、`match.json`）

尾→串阻 16 段 P−N 全部 0.000 mm。串阻→触点：南岛、北岛、B 片全部 0.000 mm；**A CH1、CH2 电极侧 P 1.29 / N 1.09，差 0.200 mm = 7.874 mil**（≤ 10 mil 过，盒底照抄 R12）。

| 片 | 通道 | 尾→串阻 P = N（mm） |
|---|---|---|
| A | CH1–CH8 | 33.967、42.150、47.160、59.648、71.528、82.286、92.988、100.295 |
| B | CH9–CH16 | 99.368、105.086、113.169、122.063、129.791、137.863、146.088、156.868 |

## 6. 检查（本机实跑，`checks.json` 全部 ok，`fails: []`）

| 检查 | 结果 |
|---|---|
| KiCad 10.0.6 DRC（各自 .kicad_dru） | A、B 各 **0 违规 0 未连**（`drc-a/b.json`）；`--refill-zones` 重铺后再跑也是 0/0 |
| DRC 反例（临时副本） | ① A 出盒带 CH5_N 压到 CH5_P → `tracks_crossing`；② B 并行段 CH13_P 凸到离 CH12_N 中心距 0.40 → `clearance`（规则「不同网走线中心距0.47」）；阳性对照：同处 0.47 → 不报；③ A 桥1 放 AGND 过孔 → `items_not_allowed`（动态区禁孔-A桥1） |
| 脚序反例 ④ | 对调 A 19/20、B 6/7 两根金手指的网存盘再读 → 各报 2 脚错；整排镜像 → 22 脚错 |
| route_lint 硬项 | A、B 均 0；`pad_exit_side` 各 40 只报告（0402 沿元件轴出线，同 R12/R14） |
| 几何（读文件） | 不同网线最小中心距 A 0.500 / B 0.4825；对内 0.300；线铜到外形 A 0.315 / B 0.312，到让位孔边 A 0.375 / B 0.325；动态区过孔 0；过孔 A 55、B 61 |
| 尾部过孔到金手指 | 过孔铜到金手指铜最小 A 4.30 / B 4.90，孔边到金手指焊盘边 A 4.425 / B 5.025（工程孔到铜规则 0.2） |
| 串阻焊盘到触点焊盘 | 南岛（A CH5–8、B CH9–16）N/P 和盒底 P 侧（R1、R3）**0.12**；盒底 N 侧 R2/R4 电极侧焊盘与同网触点焊盘相连（−0.08）；北岛 1.6–2.3；两颗 200k 2.6 以上。与 R12 逐颗同值 |
| 岛补强 | B 面 PI，每岛 `cx±2.4 × 39.6–60.4`（宽 **20.8 mm**，PCB 岛宽 **21.2 mm**）；**28 个岛触点焊盘（Ø1.0 端子孔外到 Ø1.8 边）100% 盖住**；串阻焊盘被盖 0 |
| GND 平面 | 每层 1 块连通铜，孤铜 0、< 0.5 mm² 碎块 0、< 0.15 碎孔 0（最窄孔 0.42）；动态区菱形网格实铜 / 可铺铜面积 A 0.51–0.61、B 0.52–0.59 |
| 两片叠放（`stack_clearance`，两向） | B 外形 vs A 串阻焊盘最小 **0.30 mm**（盒底 `R2.1`；南岛 N 串阻外扩后与 B 并行带净距增至 **1.292 mm**）；让位孔 vs 辅助触点焊盘 **0.20 mm** |
| 正背面走线经过串阻焊盘 | **盒外 14 岛全部 0 处**（B 片全板 **0 处**；A 片仅盒底 `R1/R3/R33` 6 焊盘 13 处） |
| 检查不改板 | 检查前后两块板 SHA256 不变 |

## 7. PNG 预览（`preview.py` 生成）

- 全貌：`preview-a.png`、`preview-b.png`
- 并行段放大：`preview-a-band.png`、`preview-b-band.png`、`preview-b-islands.png`
- 同一 TPU 槽两片叠看：`preview-slot.png`
- 岛补强：`preview-a-stiffener.png`；动态区网格地：`preview-a-gnd.png`

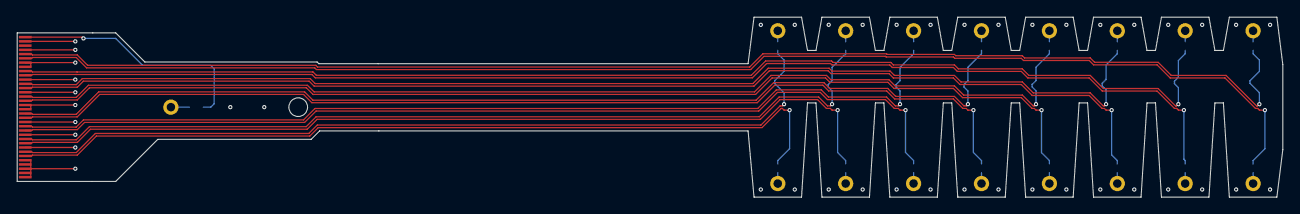
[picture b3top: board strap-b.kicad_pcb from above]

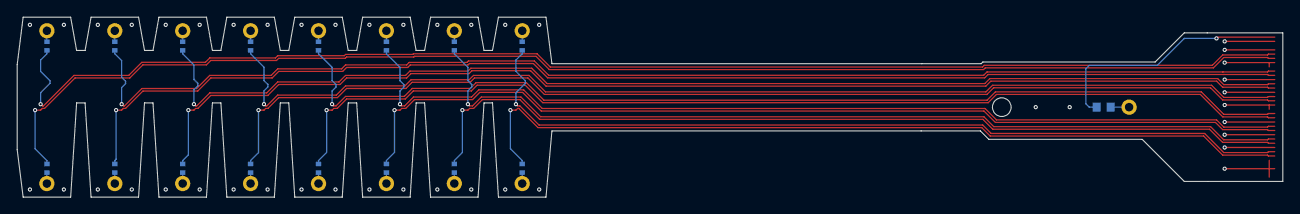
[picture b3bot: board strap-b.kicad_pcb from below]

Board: 4 copper layers, 149.1 x 21.2 mm, 35 parts (17 on the bottom side), 35 nets.

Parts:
E9N, E9P, E10N, E10P, E11N, E11P, E12N, E12P, E13N, E13P, E14N, E14P, E15N, E15P, E16N, E16P: 贴肤触点; CONTACT_D1.8
EB2: 贴肤触点; CONTACT_D1.8
R17, R18, R19, R20, R21, R22, R23, R24, R25, R26, R27, R28, R29, R30, R31, R32: 100k; R0402
R34: 200k; R0603
TAIL_B: D17 V4_FPC3; FPC34_P0.5_TAIL

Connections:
AGND: TAIL_B.1, TAIL_B.2, TAIL_B.3, TAIL_B.4, TAIL_B.5, TAIL_B.8, TAIL_B.11, TAIL_B.14, TAIL_B.17, TAIL_B.18, TAIL_B.21, TAIL_B.24, TAIL_B.27, TAIL_B.28, TAIL_B.31, TAIL_B.33
BIAS_DRV12: R34.1, TAIL_B.34
BIAS_DRV12_E: EB2.1, R34.2
CH9_N: R18.1, TAIL_B.7
CH9_N_E: E9N.1, R18.2
CH9_P: R17.1, TAIL_B.6
CH9_P_E: E9P.1, R17.2
CH10_N: R20.1, TAIL_B.10
CH10_N_E: E10N.1, R20.2
CH10_P: R19.1, TAIL_B.9
CH10_P_E: E10P.1, R19.2
CH11_N: R22.1, TAIL_B.13
CH11_N_E: E11N.1, R22.2
CH11_P: R21.1, TAIL_B.12
CH11_P_E: E11P.1, R21.2
CH12_N: R24.1, TAIL_B.16
CH12_N_E: E12N.1, R24.2
CH12_P: R23.1, TAIL_B.15
CH12_P_E: E12P.1, R23.2
CH13_N: R26.1, TAIL_B.20
CH13_N_E: E13N.1, R26.2
CH13_P: R25.1, TAIL_B.19
CH13_P_E: E13P.1, R25.2
CH14_N: R28.1, TAIL_B.23
CH14_N_E: E14N.1, R28.2
CH14_P: R27.1, TAIL_B.22
CH14_P_E: E14P.1, R27.2
CH15_N: R30.1, TAIL_B.26
CH15_N_E: E15N.1, R30.2
CH15_P: R29.1, TAIL_B.25
CH15_P_E: E15P.1, R29.2
CH16_N: R32.1, TAIL_B.30
CH16_N_E: E16N.1, R32.2
CH16_P: R31.1, TAIL_B.29
CH16_P_E: E16P.1, R31.2
